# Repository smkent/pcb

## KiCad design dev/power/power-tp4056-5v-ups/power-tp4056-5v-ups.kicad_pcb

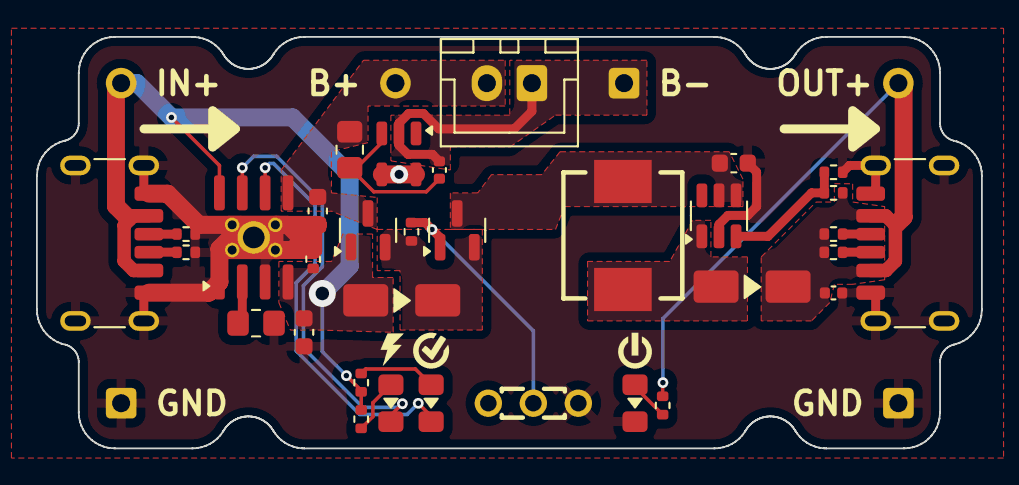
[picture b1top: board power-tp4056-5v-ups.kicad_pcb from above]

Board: 2 copper layers, 52.5 x 22.9 mm, 39 parts (0 on the bottom side), 21 nets.

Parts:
BT1: Battery_Cell; JST_XH_B2B-XH-A_1x02_P2.50mm_Vertical_simple_pad2gnd
C1, C2, C4: 10uF; C_0603_1608Metric
C3: 0.1uF; C_0402_1005Metric
C5: 10uF; C_0402_1005Metric
D1, D2: SS34; D_SMA_simple
J0, J1: USB_C_Receptacle_PowerOnly_6P; USB_C_Receptacle_GCT_USB4125-xx-x_6P_TopMnt_Horizontal_hand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
J101, J201, J301: Conn_01x01; PinHeader_1x01_P2.54mm_simple
J102, J202, J302: Conn_01x01; PinHeader_1x01_P2.54mm_simple_square
L1: 22uH; IND-SMD_L7.0-W6.6
LED1: Charge; LED_0805_2012Metric_Pad1.15x1.40mm_HandSolder_simple
LED2: Done; LED_0805_2012Metric_Pad1.15x1.40mm_HandSolder_simple
LED3: Boost; LED_0805_2012Metric_Pad1.15x1.40mm_HandSolder_simple
Q1, Q2: AO3401A; SOT-23
R1: 1K2; R_0805_2012Metric_Pad1.20x1.40mm_HandSolder
R2: 100R; R_0805_2012Metric_Pad1.20x1.40mm_HandSolder
R3: 75K; R_0402_1005Metric
R4, R5, R12, R13: 5K1; R_0402_1005Metric
R6, R7: 22K; R_0402_1005Metric
R8, R9, R10, R11: 10K; R_0402_1005Metric
SW1: SW_SPDT; SW-TH_DEALON_SS-12D01-GX_simple
U1: TP4056; SOIC-8-1EP_3.9x4.9mm_P1.27mm_EP2.41x3.3mm_ThermalVias_Custo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
U2: XB5350D0; SOT-23-5_simple
U3: MT3608; SOT-23-6

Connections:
B+: BT1.1 (+), C2.2, J301.1, Q1.3 (D), R2.1, U1.5 (BAT)
B-: BT1.2 (-), C3.1, J302.1, U2.2 (GND)
BATVDD: C3.2, R2.2, U2.3 (VDD)
BOOST: C4.1, L1.1, Q2.3 (D), U3.4 (EN), U3.5 (IN)
FB: R3.2, R10.1, U3.3 (FB)
GND: C1.2, C2.1, C4.2, C5.2, J0.A12 (GND), J0.B12 (GND), J0.S1 (SHIELD), J1.A12 (GND), J1.B12 (GND), J1.S1 (SHIELD), J102.1, J202.1, LED3.1 (K), R1.2, R4.2, R5.2, R10.2, R11.2, SW1.3 (C), U1.1 (TEMP), U1.3 (GND), U1.9 (EP), U2.4 (VM), U2.5 (VM), U3.2 (GND)
LOAD_SWITCH: D1.1 (K), Q1.2 (S), Q2.2 (S), R8.1
unnamed: J0.A5 (CC1), R5.1
unnamed: J0.B5 (CC2), R4.1
unnamed: J1.A5 (CC1), R7.2
unnamed: J1.B5 (CC2), R6.2
unnamed: LED1.2 (A), R12.2
unnamed: LED1.1 (K), U1.7 (~CHRG)
unnamed: LED2.2 (A), R13.2
unnamed: LED2.1 (K), U1.6 (~STDBY)
unnamed: LED3.2 (A), R9.2
unnamed: Q2.1 (G), R8.2, SW1.2 (B)
unnamed: R1.1, U1.2 (PROG)
SW: D2.2 (A), L1.2, U3.1 (SW)
VIN: C1.1, D1.2 (A), J0.A9 (VBUS), J0.B9 (VBUS), J101.1, Q1.1 (G), R11.1, R12.1, R13.1, U1.4 (VCC), U1.8 (CE)
VOUT: C5.1, D2.1 (K), J1.A9 (VBUS), J1.B9 (VBUS), J201.1, R3.1, R6.1, R7.1, R9.1

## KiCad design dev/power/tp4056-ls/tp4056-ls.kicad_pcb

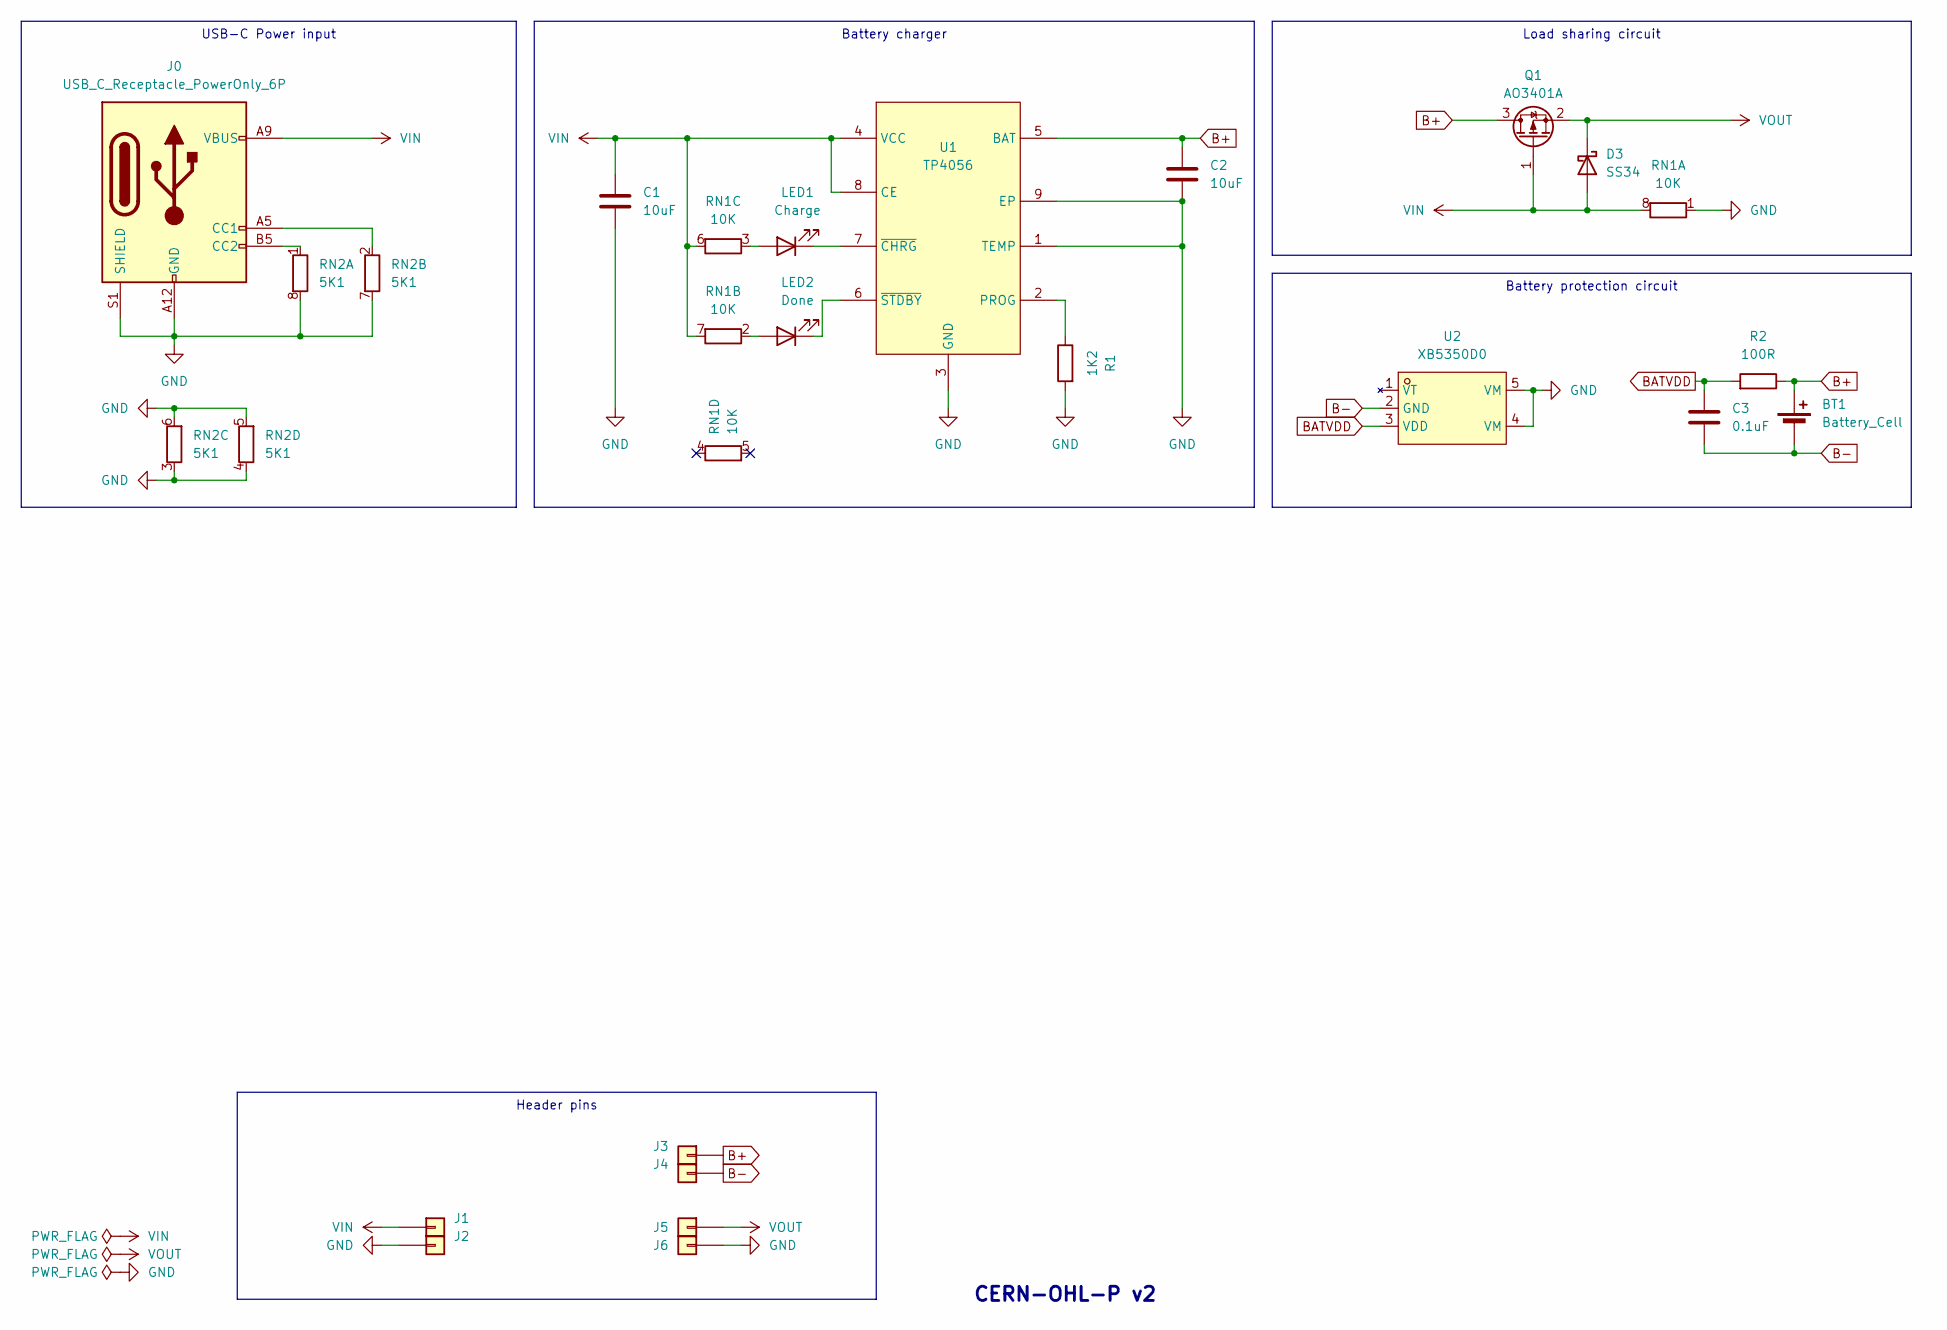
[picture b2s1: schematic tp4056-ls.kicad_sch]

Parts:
BT1: Battery_Cell; JST_XH_B2B-XH-A_1x02_P2.50mm_Vertical_simple
C1, C2: 10uF; C_0805_2012Metric_Pad1.18x1.45mm_HandSolder; LCSC Part C15850
C3: 0.1uF; C_0805_2012Metric_Pad1.18x1.45mm_HandSolder; LCSC Part C28233
D3: SS34; D_SMA_simple; LCSC Part C8678
J0: USB_C_Receptacle_PowerOnly_6P; USB_C_Receptacle_GCT_USB4125-xx-x_6P_TopMnt_Horizontal_hand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
J1, J3, J5: Conn_01x01; PinHeader_1x01_P2.54mm_simple
J2, J4, J6: Conn_01x01; PinHeader_1x01_P2.54mm_simple_square
LED1: Charge; LED_0805_2012Metric_Pad1.15x1.40mm_HandSolder_simple
LED2: Done; LED_0805_2012Metric_Pad1.15x1.40mm_HandSolder_simple
Q1: AO3401A; SOT-23; LCSC Part C15127
R1: 1K2; R_0805_2012Metric_Pad1.20x1.40mm_HandSolder; LCSC Part C17379
R2: 100R; R_0805_2012Metric_Pad1.20x1.40mm_HandSolder; LCSC Part C17408
RN1: 10K; R_Array_Convex_4x0603; LCSC Part C29718
RN2: 5K1; R_Array_Convex_4x0603
U1: TP4056; SOIC-8-1EP_3.9x4.9mm_P1.27mm_EP2.41x3.3mm_ThermalVias_Custo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; JLCPCB_CORRECTION 0; 0; 270
U2: XB5350D0; SOT-23-5_simple; JLCPCB_CORRECTION 0; 0; 270

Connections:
B+: BT1.1 (+), C2.2, J3.1, Q1.3 (D), R2.1, U1.5 (BAT)
B-: BT1.2 (-), C3.1, J4.1, U2.2 (GND)
BATVDD: C3.2, R2.2, U2.3 (VDD)
GND: C1.2, C2.1, J0.A12 (GND), J0.B12 (GND), J0.S1 (SHIELD), J2.1, J6.1, R1.2, RN1.1 (R1.1), RN2.3 (R3.1), RN2.4 (R4.1), RN2.5 (R4.2), RN2.6 (R3.2), RN2.7 (R2.2), RN2.8 (R1.2), U1.1 (TEMP), U1.3 (GND), U1.9 (EP), U2.4 (VM), U2.5 (VM)
unnamed: J0.A5 (CC1), RN2.2 (R2.1)
unnamed: J0.B5 (CC2), RN2.1 (R1.1)
unnamed: LED1.2 (A), RN1.3 (R3.1)
unnamed: LED1.1 (K), U1.7 (~CHRG)
unnamed: LED2.2 (A), RN1.2 (R2.1)
unnamed: LED2.1 (K), U1.6 (~STDBY)
unnamed: R1.1, U1.2 (PROG)
VIN: C1.1, D3.2 (A), J0.A9 (VBUS), J0.B9 (VBUS), J1.1, Q1.1 (G), RN1.6 (R3.2), RN1.7 (R2.2), RN1.8 (R1.2), U1.4 (VCC), U1.8 (CE)
VOUT: D3.1 (K), J5.1, Q1.2 (S)

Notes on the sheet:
Header pins
Battery protection circuit
USB-C Power input
Load sharing circuit
Battery charger
CERN-OHL-P v2

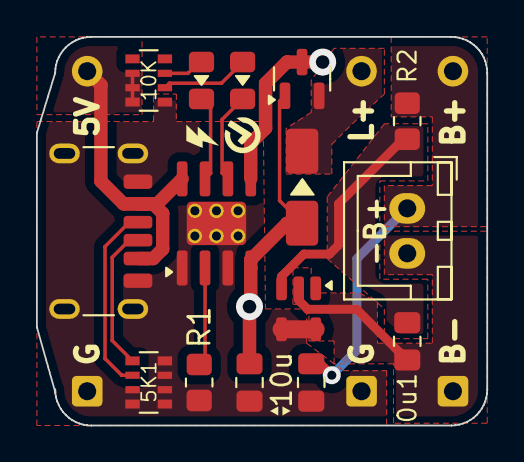
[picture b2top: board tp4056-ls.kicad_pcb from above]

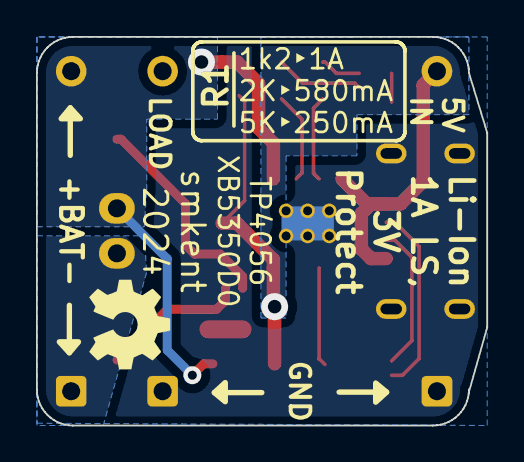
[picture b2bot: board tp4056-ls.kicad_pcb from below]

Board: 2 copper layers, 25.0 x 21.6 mm, 21 parts (6 on the bottom side), 13 nets.

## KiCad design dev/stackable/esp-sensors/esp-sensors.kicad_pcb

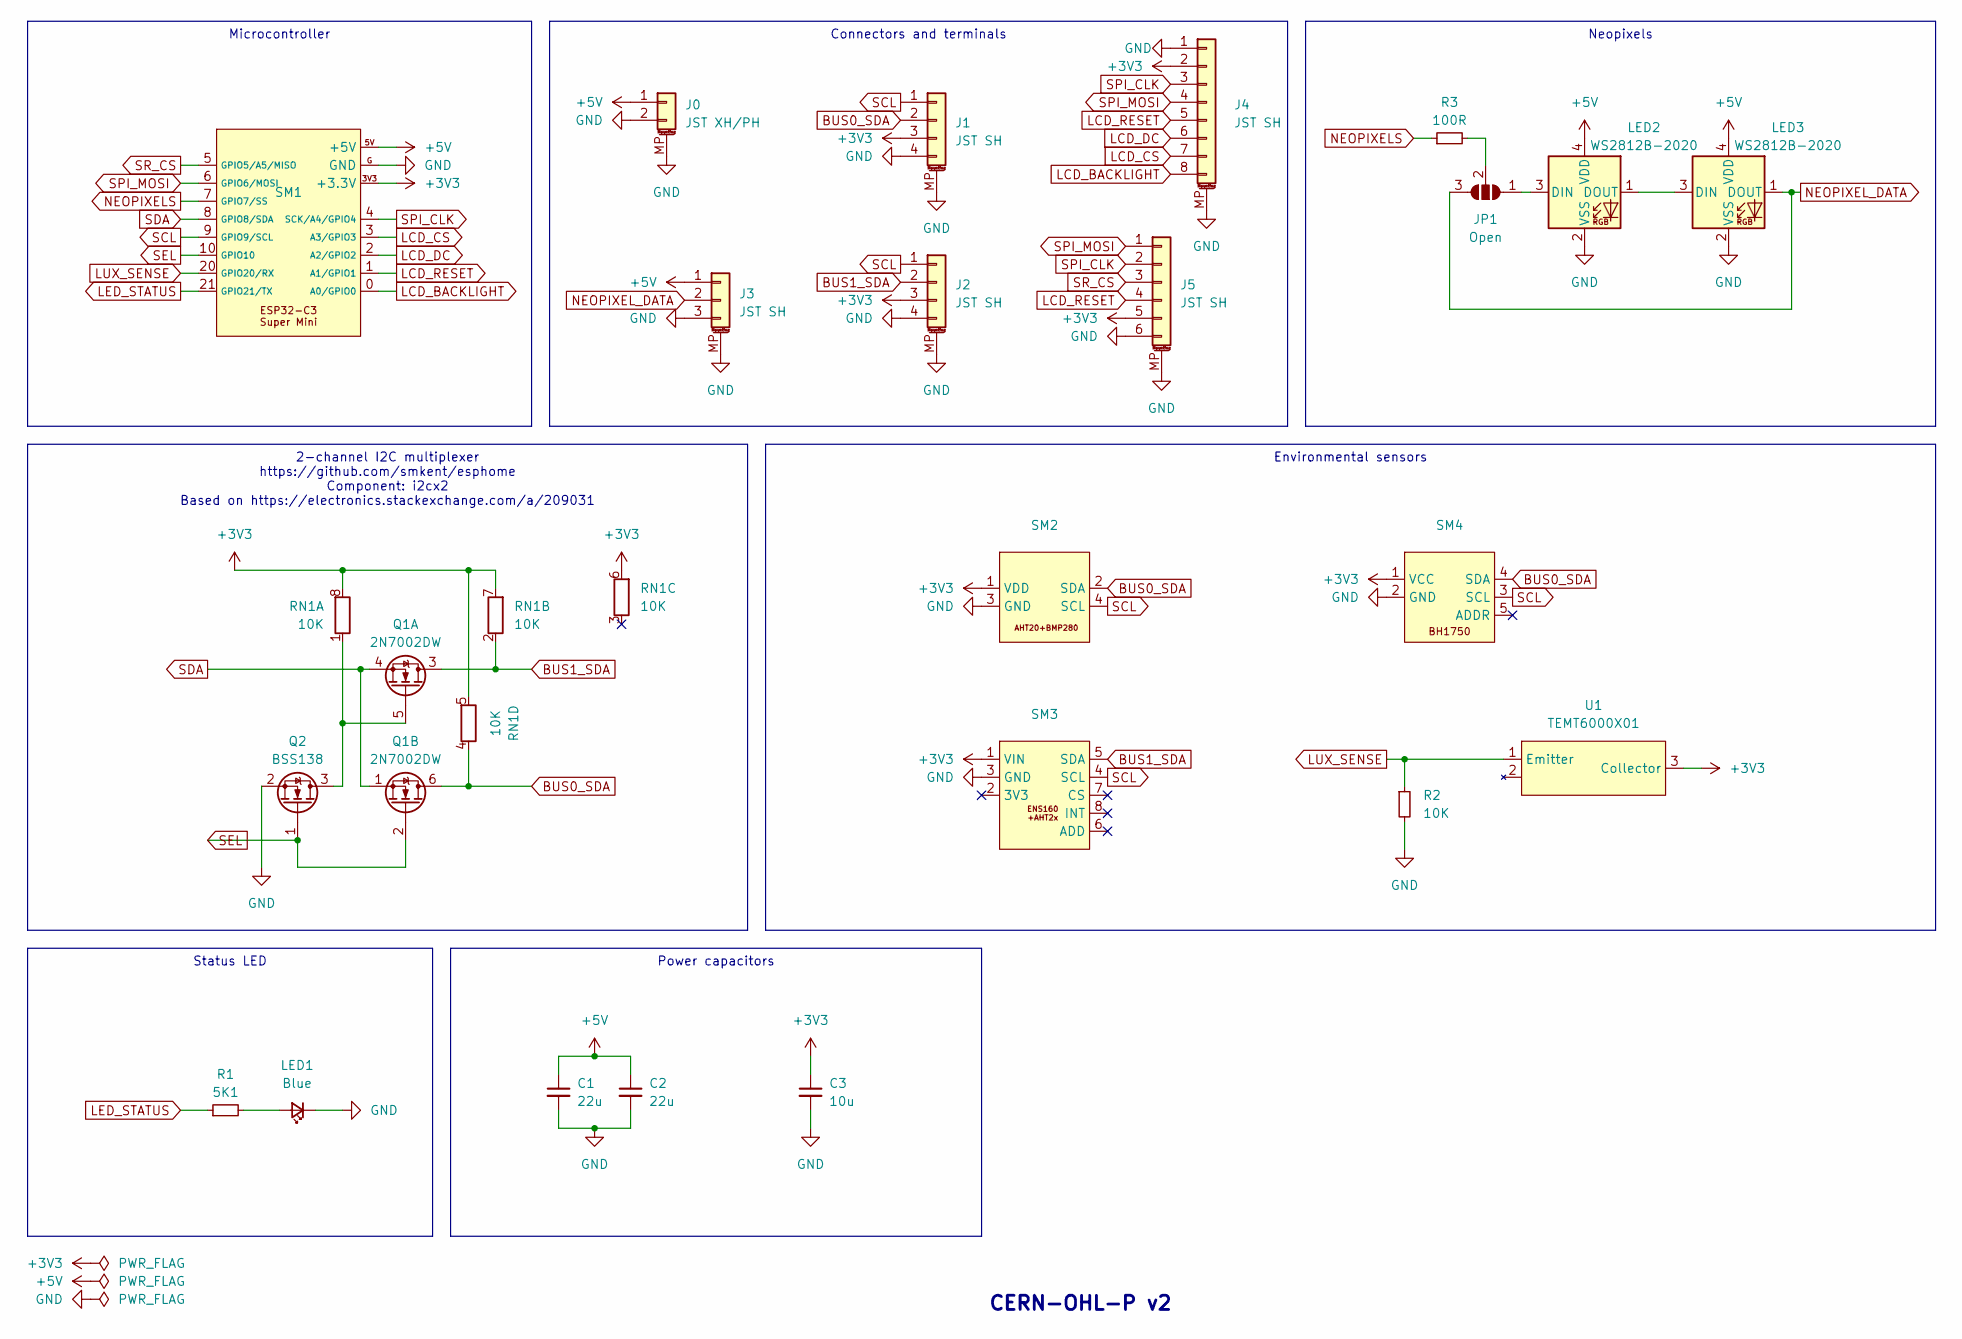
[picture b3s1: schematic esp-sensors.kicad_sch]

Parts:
C1, C2: 22u; C_0805_2012Metric_Pad1.18x1.45mm_HandSolder
C3: 10u; C_0603_1608Metric_Pad1.08x0.95mm_HandSolder
J0: JST XH/PH; Conn_Combo_JST-1x02-XH_PH-SMD-pad2gnd
J1, J2: JST SH; JST_SH_SM04B-SRSS-TB_1x04-1MP_P1.00mm_Horizontal
J3: JST SH; JST_SH_SM03B-SRSS-TB_1x03-1MP_P1.00mm_Horizontal
J4: JST SH; JST_SH_SM08B-SRSS-TB_1x08-1MP_P1.00mm_Horizontal
J5: JST SH; JST_SH_SM06B-SRSS-TB_1x06-1MP_P1.00mm_Horizontal
JP1: Open; SolderJumper-3_P1.3mm_Open_RoundedPad1.0x1.5mm
LED1: Blue; LED_0603_1608Metric_Pad1.05x0.95mm_HandSolder_simple
LED2, LED3: WS2812B-2020; LED-SMD_4P-L2.0-W2.0-BR-1
Q1: 2N7002DW; SOT-23-6; LCSC Part C5190214
Q2: BSS138; SOT-23
R1: 5K1; R_0603_1608Metric_Pad0.98x0.95mm_HandSolder_simple
R2: 10K; R_0603_1608Metric_Pad0.98x0.95mm_HandSolder_simple
R3: 100R; R_0603_1608Metric_Pad0.98x0.95mm_HandSolder
RN1: 10K; R_Array_Convex_4x0603
SM1: ESP32-C3-Super-Mini-Castellated-SMD
SM2: PinSocket_1x04_P2.54mm_Horizontal_descending_simple
SM3: PinSocket_1x08_P2.54mm_Horizontal_descending_simple
SM4: PinSocket_1x05_P2.54mm_Horizontal_simple
U1: TEMT6000X01; SENSORS-SMD_TEMT6000X01_HandSolder; LCSC Part C94098

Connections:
+3V3: C3.1, J1.3, J2.3, J4.2, J5.5, RN1.5 (R4.2), RN1.6 (R3.2), RN1.7 (R2.2), RN1.8 (R1.2), SM1.3V3 (+3.3V), SM2.1 (VDD), SM3.1 (VIN), SM4.1 (VCC), U1.3 (Collector)
+5V: C1.1, C2.1, J0.1, J3.1, LED2.4 (VDD), LED3.4 (VDD), SM1.5V (+5V)
BUS0_SDA: J1.2, Q1.6 (D), RN1.4 (R4.1), SM2.2 (SDA), SM4.4 (SDA)
BUS1_SDA: J2.2, Q1.3 (D), RN1.2 (R2.1), SM3.5 (SDA)
GND: C1.2, C2.2, C3.2, J0.2, J0.MP (MountPin), J1.4, J1.MP (MountPin), J2.4, J2.MP (MountPin), J3.3, J3.MP (MountPin), J4.1, J4.MP (MountPin), J5.6, J5.MP (MountPin), LED1.1 (K), LED2.2 (VSS), LED3.2 (VSS), Q2.2 (S), R2.2, SM1.G (GND), SM2.3 (GND), SM3.3 (GND), SM4.2 (GND)
LCD_BACKLIGHT: J4.8, SM1.0 (A0/GPIO0)
LCD_CS: J4.7, SM1.3 (A3/GPIO3)
LCD_DC: J4.6, SM1.2 (A2/GPIO2)
LCD_RESET: J4.5, J5.4, SM1.1 (A1/GPIO1)
LED_STATUS: R1.1, SM1.21 (GPIO21/TX)
LUX_SENSE: R2.1, SM1.20 (GPIO20/RX), U1.1 (Emitter)
NEOPIXELS: R3.1, SM1.7 (GPIO7/SS)
NEOPIXEL_DATA: J3.2, JP1.3 (B), LED3.1 (DOUT)
unnamed: JP1.1 (A), LED2.3 (DIN)
unnamed: JP1.2 (C), R3.2
unnamed: LED1.2 (A), R1.2
unnamed: LED2.1 (DOUT), LED3.3 (DIN)
unnamed: Q1.5 (G), Q2.3 (D), RN1.1 (R1.1)
SCL: J1.1, J2.1, SM1.9 (GPIO9/SCL), SM2.4 (SCL), SM3.4 (SCL), SM4.3 (SCL)
SDA: Q1.1 (S), Q1.4 (S), SM1.8 (GPIO8/SDA)
SEL: Q1.2 (G), Q2.1 (G), SM1.10 (GPIO10)
SPI_CLK: J4.3, J5.2, SM1.4 (SCK/A4/GPIO4)
SPI_MOSI: J4.4, J5.1, SM1.6 (GPIO6/MOSI)
SR_CS: J5.3, SM1.5 (GPIO5/A5/MISO)

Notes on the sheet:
2-channel I2C multiplexer https://github.com/smkent/esphome Component: i2cx2 Based on https://electronics.stackexchange.com/a/209031
Environmental sensors
Microcontroller
Power capacitors
Neopixels
Status LED
Connectors and terminals
CERN-OHL-P v2

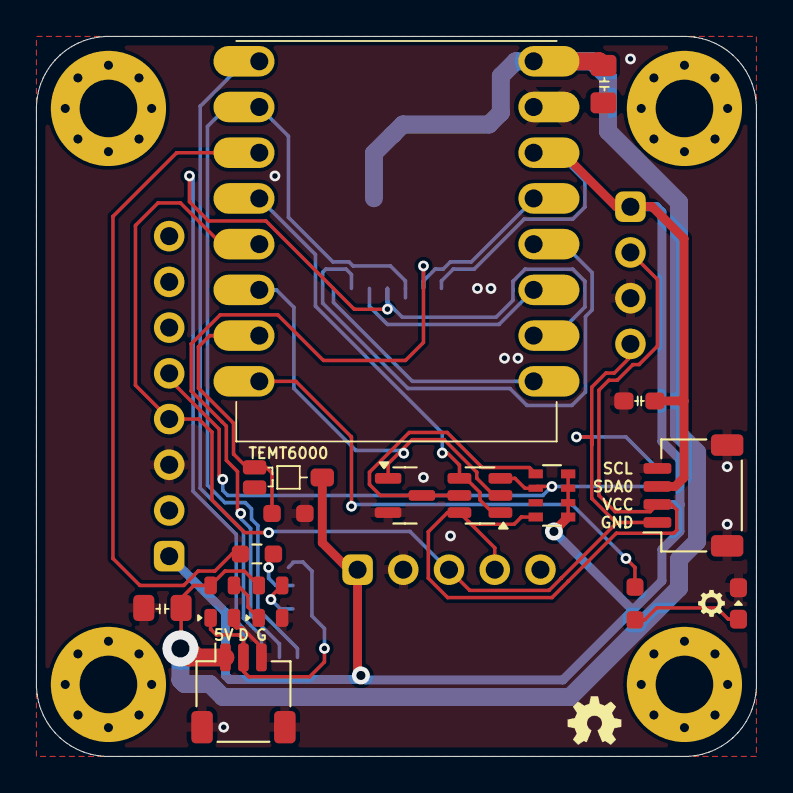
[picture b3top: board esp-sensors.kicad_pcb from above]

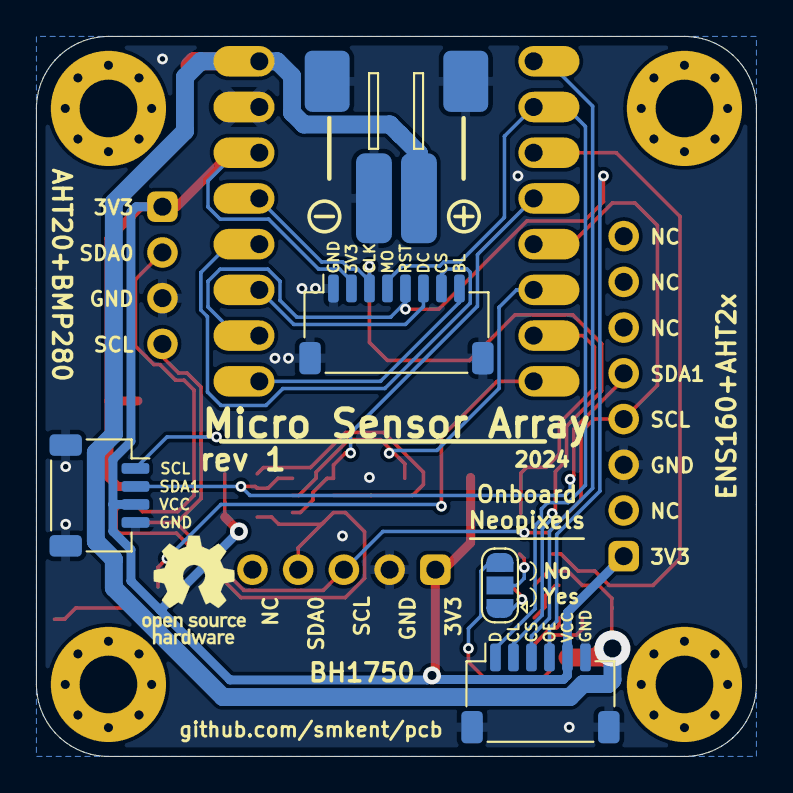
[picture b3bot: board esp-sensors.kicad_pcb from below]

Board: 2 copper layers, 40.0 x 40.0 mm, 24 parts (5 on the bottom side), 24 nets.

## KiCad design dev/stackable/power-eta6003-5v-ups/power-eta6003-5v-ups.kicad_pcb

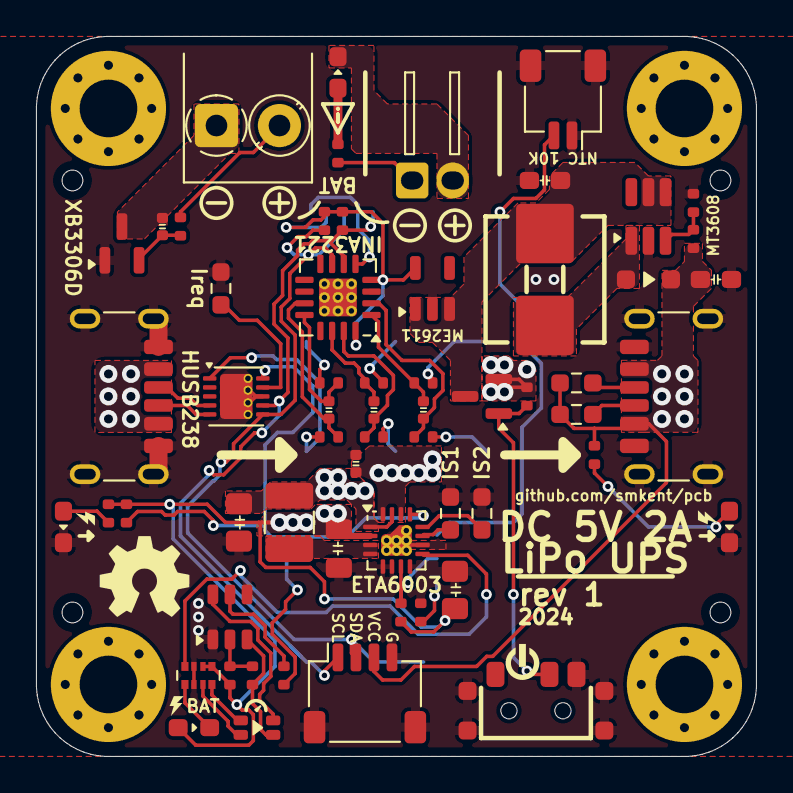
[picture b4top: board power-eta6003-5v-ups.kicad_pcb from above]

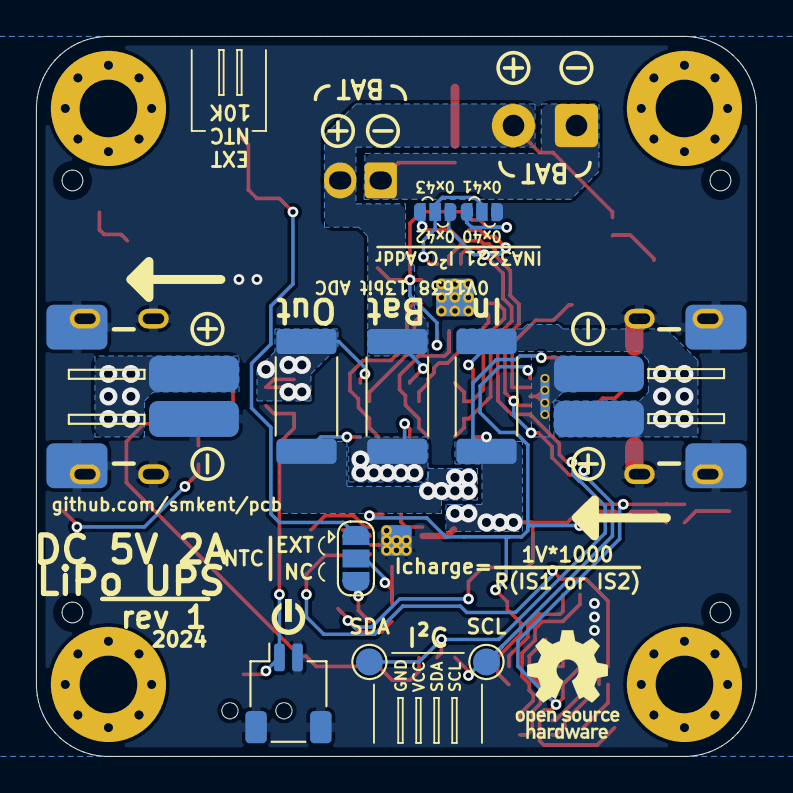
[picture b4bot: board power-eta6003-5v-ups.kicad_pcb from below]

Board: 2 copper layers, 40.0 x 40.0 mm, 71 parts (11 on the bottom side), 47 nets.

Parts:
C1: 22u; C_0805_2012Metric_Pad1.18x1.45mm_HandSolder
C2: 1u; C_0402_1005Metric_simple
C3: 10u; C_0805_2012Metric_Pad1.18x1.45mm_wide-center_HandSolder
C4, C7, C8, C9: 0u1; C_0402_1005Metric_simple
C5, C6: 10u; C_0603_1608Metric_Pad1.08x0.95mm_HandSolder
C10: 10u; C_0805_2012Metric_Pad1.18x1.45mm_HandSolder
D1: BAT60A; D_SOD-323_HandSoldering_simple
J1: P3.5; TerminalBlock_Phoenix_PT-1,5-2-3.5-H_1x02_P3.50mm_Horizonta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
J100, J200: USB_C_Receptacle_PowerOnly_6P; USB_C_Receptacle_GCT_USB4125-xx-x_6P_TopMnt_Horizontal_hand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
J101, J201: JST XH/PH; Conn_Combo_JST-1x02-XH_PH-SMD-alt-pad2gnd
J300: JST XH/PH; Conn_Combo_JST-1x02-XH_PH-THT-pad2gnd
J301, J500: JST SH; JST_SH_SM02B-SRSS-TB_1x02-1MP_P1.00mm_Horizontal
J400: JST SH; JST_SH_SM04B-SRSS-TB_1x04-1MP_P1.00mm_Horizontal
JP1: NTC; SolderJumper-3_P1.3mm_Open_RoundedPad1.0x1.5mm
JP2, JP3: VS/GND; SolderJumper-3_P1.0mm_Open_RoundedPad_simple
L1: 2u2; L_1210_3225Metric_Pad1.42x2.65mm_HandSolder
L2: 4u7; Inductor_Multi_7.0x6.6_1210
LED1: Pink; LED_0603_1608Metric_Pad1.05x0.95mm_HandSolder_simple
LED2: LED; LED-ARRAY-SMD_4P-L2.0-W1.3-RD
LED3: White; LED_0603_1608Metric_Pad1.05x0.95mm_HandSolder_simple
LED4: Red; LED_0603_1608Metric_Pad1.05x0.95mm_HandSolder_simple
LED5: Blue; LED_0603_1608Metric_Pad1.05x0.95mm_HandSolder_simple
Q1: 2N7002DW; SOT-23-6_trimmed-pads_simple
Q2: AO3401A; SOT-23_simple
R1, R2, R8, R9, R10, R13, R25, R104: 10K; R_0402_1005Metric_simple
R3, R11, R103: 5K1; R_0402_1005Metric_simple
R4: 2K; R_0603_1608Metric_Pad0.98x0.95mm_HandSolder
R5: 1K; R_0603_1608Metric_Pad0.98x0.95mm_HandSolder
R6, R7, R27, R28, R29, R30, R31, R32: 10R; R_0402_1005Metric_simple
R12: 100R; R_0402_1005Metric_simple
R24: 75K; R_0402_1005Metric_simple
R102, R201, R202: 22K; R_0603_1608Metric_Pad0.98x0.95mm_HandSolder
RN1: 5K1; R_Array_Convex_4x0402
SR1, SR2, SR3: R040; R_2512_6332Metric_Pad1.40x3.35mm_HandSolder
SW1: SW_SPDT; SW-SMD_3P-P1.50_L2.7-W6.6
TP1, TP2: TestPoint_Pad_D1.5mm
U1: ETA6003; ETA6003_QFN-16-1EP_3x3mm_P0.5mm_EP1.7x1.7mm_ThermalVias
U2: XB3306D; SOT-23_simple
U3: ME6211C33M5; SOT-23-5_simple
U4: INA3221; Texas_RGV0016A_VQFN-16-1EP_4x4mm_P0.65mm_EP2.1x2.1mm_Therma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
U5: MT3608; SOT-23-6_Handsoldering_simple
U101: HUSB238_002DD; WDFN-10-1EP_3x3mm_P0.5mm_EP1.8x2.5mm_ThermalVias_half

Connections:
+3V3: JP2.1 (A), R8.1, R9.1, U3.5 (V_{OUT}), U4.4 (VS), U4.16 (VPU)
B+: J1.1, J300.1, LED4.1 (K), R12.2, R30.2, SR2.1
B-: C4.2, J1.2, J300.2, R11.2, U2.3 (GND)
BAT_SHUNT: C2.1, R29.2, SR2.2, U1.14 (BATT), U1.16 (BATT)
BOOST_SW: D1.2 (A), L2.2, U5.1 (SW)
EXT_POWER_SWITCH: J500.1, Q2.1 (G), R10.2, SW1.2 (B)
FB: R24.2, R25.1, U5.3 (FB)
GND: C1.2, C2.2, C3.1, C5.2, C6.2, C10.1, J100.A12 (GND), J100.B12 (GND), J100.S1 (SHIELD), J101.2, J101.MP (MountPin), J200.A12 (GND), J200.B12 (GND), J200.S1 (SHIELD), J201.2, J201.MP (MountPin), J301.1, J301.MP (MountPin), J400.4, J400.MP (MountPin), J500.2, J500.MP (MountPin), JP2.3 (B), LED3.1 (K), LED5.1 (K), Q1.1 (S), Q1.4 (S), R2.1, R4.2, R5.2, R25.2, R102.2, RN1.2 (R2.1), RN1.7 (R2.2), SW1.3 (C), SW1.MP (MountPin), U1.5 (PGND), U1.6 (ENB), U1.8 (ENPPB), U1.10 (GND), U1.17 (EP), U2.1 (VM), U3.2 (V_{SS}), U4.3 (GND), U5.2 (GND), U101.8 (VSET), U101.11 (GND)
LOAD_SHUNT: C1.1, L1.1, R31.2, SR3.2, U1.1 (SYS), U1.15 (SYS)
LOAD_SHUNT_OUT: Q2.2 (S), R10.1, R32.2, SR3.1
NTC: JP1.2 (C), R1.1, U1.7 (NTC)
NTC_CONN: J301.2, JP1.1 (A)
unnamed: J100.A5 (CC1), U101.4 (CC1)
unnamed: J100.B5 (CC2), U101.5 (CC2)
unnamed: J200.A5 (CC1), R201.2
unnamed: J200.B5 (CC2), R202.2
unnamed: JP1.3 (B), R2.2
unnamed: JP2.2 (C), JP3.2 (C), U4.5 (A0)
unnamed: LED1.1 (K), RN1.1 (R1.1)
unnamed: LED2.1 (RED_A), RN1.3 (R3.1)
unnamed: LED2.2 (RED_K), Q1.3 (D), R7.1
unnamed: LED2.3 (BLUE_A), RN1.4 (R4.1)
unnamed: LED2.4 (BLUE_K), Q1.6 (D)
unnamed: LED3.2 (A), R103.2
unnamed: LED4.2 (A), R11.1
unnamed: LED5.2 (A), R3.2
unnamed: Q1.5 (G), R6.1
unnamed: Q1.2 (G), R7.2, R13.2
unnamed: RN1.8 (R1.2), U1.9 (STAT)
unnamed: R4.1, U1.11 (ISET1)
unnamed: R5.1, U1.12 (ISET2)
unnamed: C4.1, R12.1, U2.2 (VDD)
unnamed: C7.1, R27.2, U4.12 (IN+1)
unnamed: C8.1, R29.1, U4.15 (IN+2)
unnamed: C9.1, R31.1, U4.2 (IN+3)
unnamed: C7.2, R28.2, U4.11 (IN-1)
unnamed: C8.2, R30.1, U4.14 (IN-2)
unnamed: C9.2, R32.1, U4.1 (IN-3)
unnamed: R102.1, U101.9 (ISET)
SCL: J400.1, JP3.1 (A), R9.2, TP1.1, U4.6 (SCL), U101.7 (SCL)
SDA: J400.2, JP3.3 (B), R8.2, TP2.1, U4.7 (SDA), U101.6 (SDA)
SW: L1.2, U1.3 (SW), U1.4 (SW)
USB_DET: R6.2, R104.2, U1.13 (USB_DET), U101.10 (GATE)
VIN: J100.A9 (VBUS), J100.B9 (VBUS), J101.1, R27.1, SR1.1
VIN_SHUNT: C3.2, C10.2, LED1.2 (A), R1.2, R13.1, R28.1, R103.1, R104.1, RN1.5 (R4.2), RN1.6 (R3.2), SR1.2, U1.2 (IN), U101.1 (VIN)
VOUT: C6.1, D1.1 (K), J200.A9 (VBUS), J200.B9 (VBUS), J201.1, J400.3, R3.1, R24.1, R201.1, R202.1
VSYS: C5.1, L2.1, Q2.3 (D), U3.1 (V_{IN}), U3.3 (CE), U5.4 (EN), U5.5 (IN)

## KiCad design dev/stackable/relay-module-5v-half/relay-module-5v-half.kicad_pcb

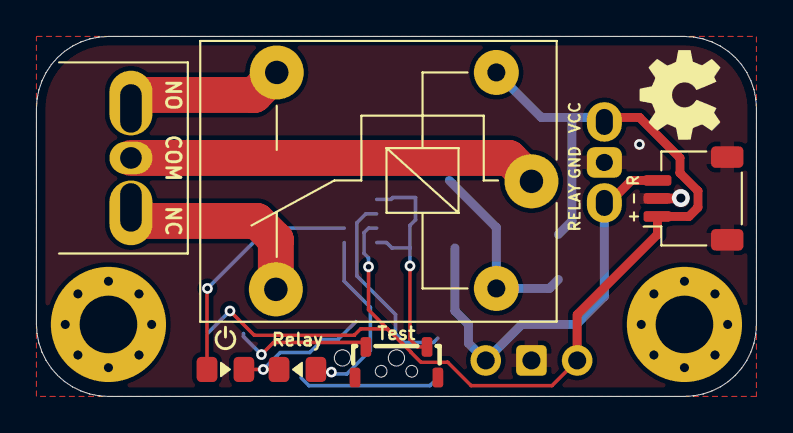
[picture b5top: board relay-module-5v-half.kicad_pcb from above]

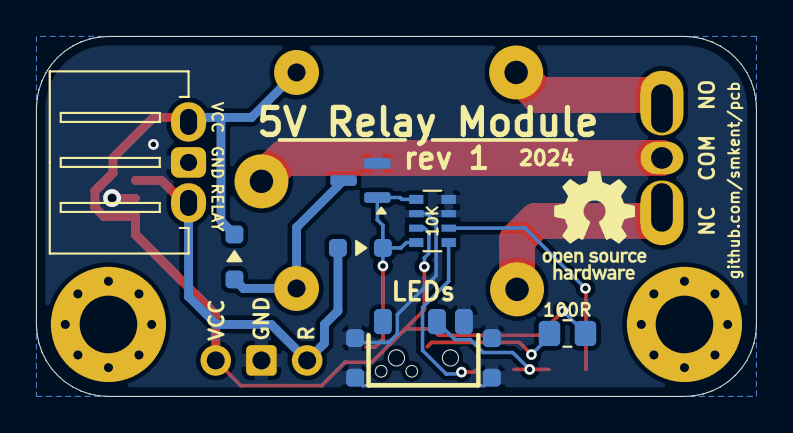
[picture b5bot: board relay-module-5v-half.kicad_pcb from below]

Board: 2 copper layers, 40.0 x 20.0 mm, 14 parts (7 on the bottom side), 12 nets.

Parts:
D1, D3: 1N4148WS; D_SOD-323_HandSoldering_simple
J0: JST SH; JST_SH_SM03B-SRSS-TB_1x03-1MP_P1.00mm_Horizontal
J1: P3.5; Conn_Combo_TerminalBlock_P3.5_JST-XH_PH_1x03
J2: JST XH/PH; Conn_Combo_JST-1x03-XH_PH-THT_pad2gnd
J10: Pin Headers; PinHeader_1x03_P2.54mm_Vertical_simple_pad2gnd
K1: Relay_SPDT; Relay_SPDT_SANYOU_SRD_Series_Form_C
LED0, LED1: LED; LED_0805_2012Metric_Pad1.15x1.40mm_HandSolder_simple
Q1: BSS138; SOT-23_simple
R1: 100R; R_0805_2012Metric_Pad1.20x1.40mm_HandSolder
RN1: 10K; R_Array_Convex_4x0603
SW0: SW_SPDT_MountingPin; SW-SMD_3P-P1.50_L2.7-W6.6
SW1: Test Button; SW-SMD_BZCN_TSA002A35XXX

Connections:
+5V: D1.1 (K), J0.1, J2.1, J10.1, K1.2, R1.2, RN1.7 (R2.2)
GND: J0.2, J0.MP (MountPin), J2.2, J10.2, Q1.2 (S), RN1.3 (R3.1), RN1.4 (R4.1), RN1.6 (R3.2), SW0.3 (C), SW0.MP (MountPin)
LED_GND: LED0.1 (K), LED1.1 (K), SW0.2 (B)
unnamed: LED0.2 (A), RN1.2 (R2.1)
unnamed: LED1.2 (A), RN1.1 (R1.1)
unnamed: R1.1, SW1.2
RELAY_1_COIL: D1.2 (A), K1.5, Q1.3 (D)
RELAY_1_CONTROL: D3.2 (A), J0.3, J2.3, J10.3
RELAY_1_MOSFET: D3.1 (K), Q1.1 (G), RN1.5 (R4.2), RN1.8 (R1.2), SW1.1
RELAY_1_SW_COMMON: J1.2, K1.1
RELAY_1_SW_NC: J1.3, K1.4
RELAY_1_SW_NO: J1.1, K1.3

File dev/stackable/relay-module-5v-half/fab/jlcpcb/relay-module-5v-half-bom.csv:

Comment,Designator,Footprint,LCSC
Pin Headers,J10,custom:PinHeader_1x03_P2.54mm_Vertical_simple_pad2gnd,
LED,"LED0,LED1",custom:LED_0805_2012Metric_Pad1.15x1.40mm_HandSolder_simple,
1N4148WS,"D1,D3",custom:D_SOD-323_HandSoldering_simple,
JST XH/PH,J2,custom:Conn_Combo_JST-1x03-XH_PH-THT_pad2gnd,
Relay_SPDT,K1,Relay_THT:Relay_SPDT_SANYOU_SRD_Series_Form_C,
P3.5,J1,custom:Conn_Combo_TerminalBlock_P3.5_JST-XH_PH_1x03,
JST SH,J0,connectors:JST_SH_SM03B-SRSS-TB_1x03-1MP_P1.00mm_Horizontal,
100R,R1,Resistor_SMD:R_0805_2012Metric_Pad1.20x1.40mm_HandSolder,
BSS138,Q1,custom:SOT-23_simple,
SW_SPDT_MountingPin,SW0,lcsc:SW-SMD_3P-P1.50_L2.7-W6.6,
Test Button,SW1,lcsc:SW-SMD_BZCN_TSA002A35XXX,
10K,RN1,Resistor_SMD:R_Array_Convex_4x0603,
